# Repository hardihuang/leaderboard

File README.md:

# leaderboard
gamification team leaderboard

more information, please visit my blog:  [hardihaung.info](http://hardihuang.info/)

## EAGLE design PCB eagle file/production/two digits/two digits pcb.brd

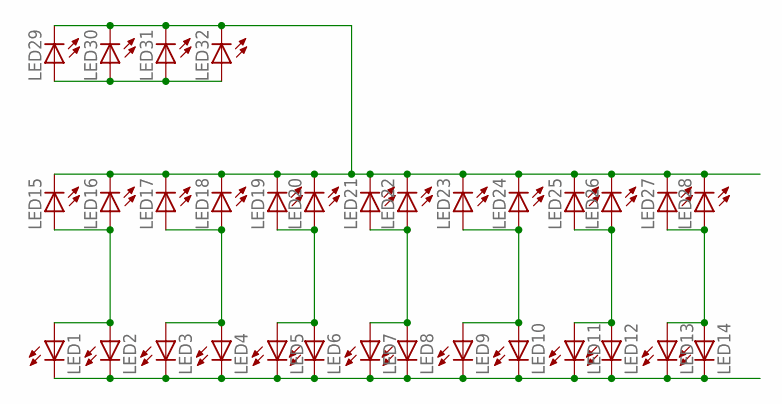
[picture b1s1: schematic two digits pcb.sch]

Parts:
LED1, LED2, LED3, LED4, LED5, LED6, LED7, LED8, LED9, LED10, LED11, LED12, LED13, LED14, LED15, LED16, LED17, LED18, LED19, LED20, LED21, LED22, LED23, LED24, LED25, LED26, LED27, LED28, LED29, LED30, LED31, LED32: LED5MM

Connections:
unnamed: LED1.K (C), LED2.K (C), LED3.K (C), LED4.K (C), LED5.K (C), LED6.K (C), LED7.K (C), LED8.K (C), LED9.K (C), LED10.K (C), LED11.K (C), LED12.K (C), LED13.K (C), LED14.K (C)
unnamed: LED1.A, LED2.A, LED15.A, LED16.A
unnamed: LED3.A, LED4.A, LED17.A, LED18.A
unnamed: LED5.A, LED6.A, LED19.A, LED20.A
unnamed: LED7.A, LED8.A, LED21.A, LED22.A
unnamed: LED9.A, LED10.A, LED23.A, LED24.A
unnamed: LED11.A, LED12.A, LED25.A, LED26.A
unnamed: LED13.A, LED14.A, LED27.A, LED28.A
unnamed: LED15.K (C), LED16.K (C), LED17.K (C), LED18.K (C), LED19.K (C), LED20.K (C), LED21.K (C), LED22.K (C), LED23.K (C), LED24.K (C), LED25.K (C), LED26.K (C), LED27.K (C), LED28.K (C), LED29.K (C), LED30.K (C), LED31.K (C), LED32.K (C)
unnamed: LED29.A, LED30.A, LED31.A, LED32.A

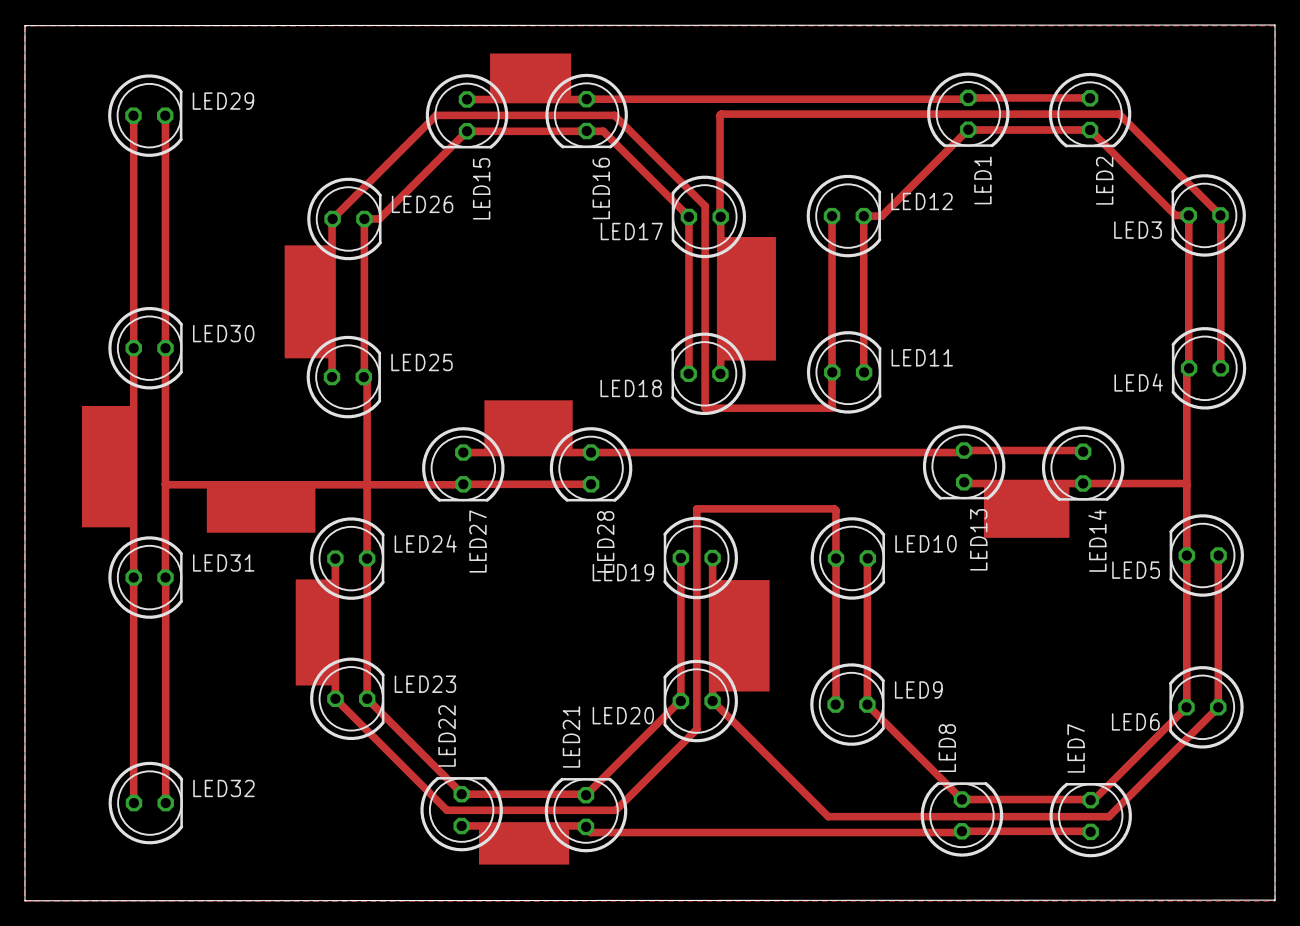
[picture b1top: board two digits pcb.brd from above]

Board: 2 copper layers, 100.0 x 70.0 mm, 32 parts (0 on the bottom side), 10 nets.

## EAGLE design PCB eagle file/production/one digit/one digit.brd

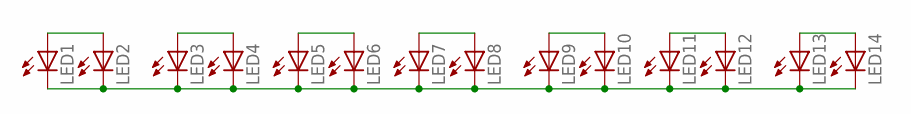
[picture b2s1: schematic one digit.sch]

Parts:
LED1, LED2, LED3, LED4, LED5, LED6, LED7, LED8, LED9, LED10, LED11, LED12, LED13, LED14: LED5MM

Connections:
unnamed: LED1.A, LED2.A
unnamed: LED3.A, LED4.A
unnamed: LED5.A, LED6.A
unnamed: LED7.A, LED8.A
unnamed: LED9.A, LED10.A
unnamed: LED11.A, LED12.A
unnamed: LED13.A, LED14.A
unnamed: LED1.K (C), LED2.K (C), LED3.K (C), LED4.K (C), LED5.K (C), LED6.K (C), LED7.K (C), LED8.K (C), LED9.K (C), LED10.K (C), LED11.K (C), LED12.K (C), LED13.K (C), LED14.K (C)

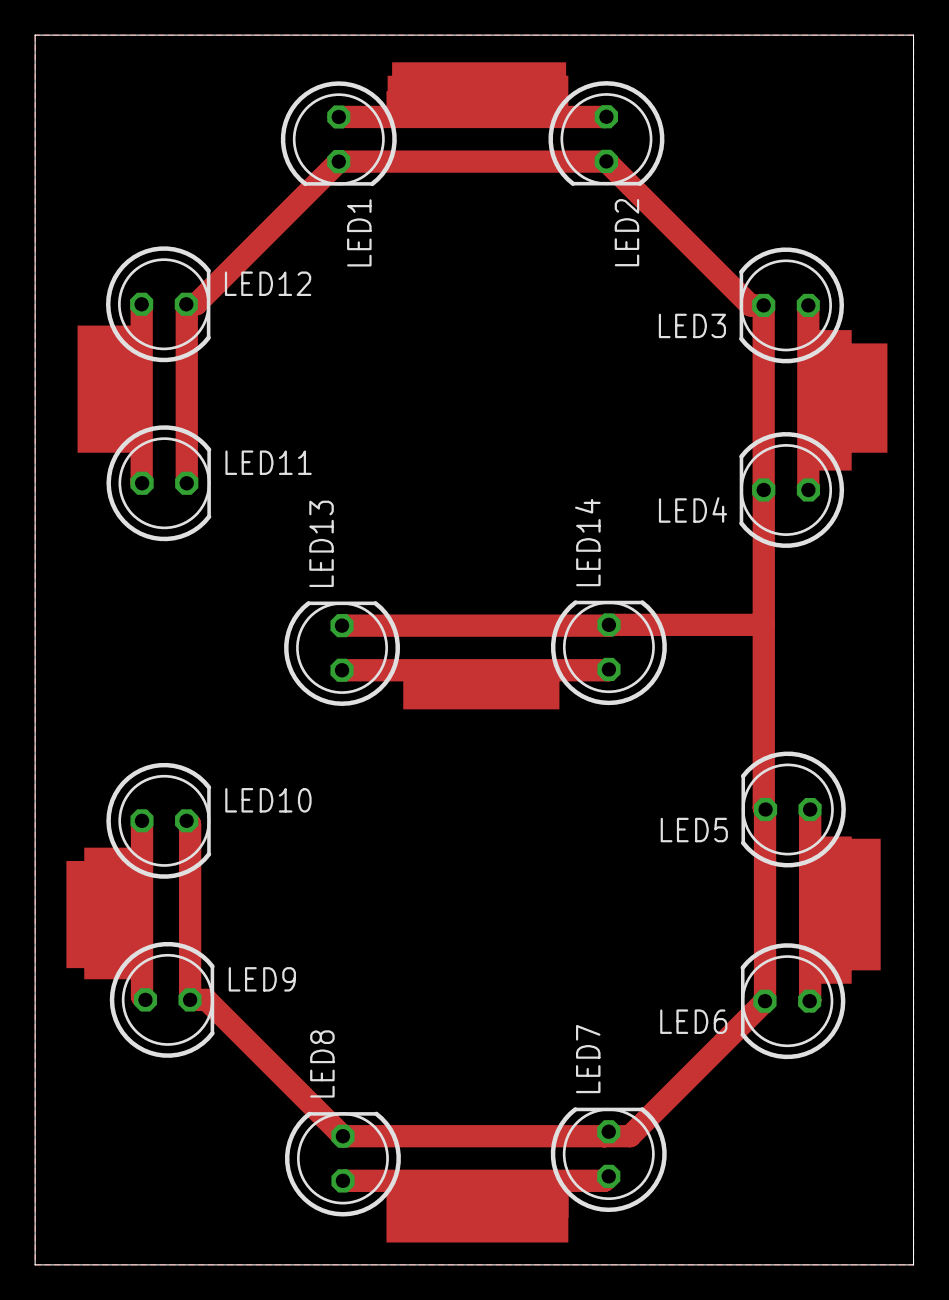
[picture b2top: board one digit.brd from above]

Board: 2 copper layers, 50.0 x 70.0 mm, 14 parts (0 on the bottom side), 8 nets.

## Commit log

2018-05-06 max7219 local test
2018-05-20 local test all the digits
2018-05-20 data in an array
2018-05-20 retrieve the data from eeprom
2018-05-21 implementing sort function
2018-05-21 added sort algorithm
2018-05-21 test array sort algorithm
2018-05-21 turn off the row if the group number is zero
2018-05-21 insert the data with 0 group number
2018-05-21 added eeprom write and read dummy data
2018-05-21 added comments and clear the score data when that group is deactivited
2018-05-22 debug
2018-05-22 test ir remote
2018-05-22 put all the code into functions
2018-05-22 controller changing the local data and updated it into eeprom
2018-05-22 added key scan if statements and some empty functions, I will write them tomorrow maybe, night
2018-05-22 changed other key to 0, so that it won't trigger the key scan
2018-05-22 added searchGroup function
2018-05-22 added add score function
2018-05-24 writing blinkGroup function
2018-05-24 added blinkGroup function
2018-05-24 debug deleteGroup function, move the data on the back forward
2018-05-24 debug delete function
2018-05-24 debug add group function, while adding group, blink the group id to wait for confirm and press # to add it
2018-05-24 added reset function
2018-05-26 fixed score 32 not display bug
2018-05-27 Version 1.0
2018-05-27 debug - score 32 blank bug
2018-05-27 added egale pcb file
2018-05-27 rename the folder
2018-06-18 Add files via upload
    new version
